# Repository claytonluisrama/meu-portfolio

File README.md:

# Meu Portfólio

Bem-vindo ao meu repositório de portfólio! Aqui você encontra uma coleção dos meus projetos acadêmicos e pessoais, demonstrando minhas habilidades e evolução profissional.

## Projetos Neste Repositório

### 1. Currículo Web (`/curriculo-web`)
[Clique aqui para acessar o site do meu Currículo Web!](https://claytonluisrama.github.io/meu-portfolio/curriculo-web/)

Um site estático desenvolvido em HTML que funciona como o meu currículo online. 
* **Tecnologias:** HTML
* **Objetivo:** Apresentar minha trajetória e habilidades de forma rápida e acessível.

### 2. Pedal de Guitarra (`/pedal-guitarra`)
Projeto de eletrônica de um pedal de guitarra.
* **Ferramentas:** KiCad
* **Objetivo:** Aplicar conhecimentos de esquemáticos e design de circuitos na prática.

---

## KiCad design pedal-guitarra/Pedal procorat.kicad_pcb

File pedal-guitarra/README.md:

# Projeto de Hardware: Pedal de Distorção (Baseado no ProCo RAT)

Este projeto é uma versão personalizada do icônico pedal de distorção **ProCo RAT**. O desenvolvimento envolveu desde o estudo do esquemático até a fabricação física da placa de circuito impresso (PCB).

## Especificações Técnicas
* **Controles:** 
  * `Gain`: Controle da intensidade da distorção.
  * `Filter`: Ajuste de corte de frequências (característica única do RAT).
  * `Volume`: Controle do nível de saída.
* **Componentes:** Resistores, capacitores (eletrolíticos e cerâmicos), diodos de clipagem e o amplificador operacional (Amp-Op).
* **Fabricação:** Placa produzida via corrosão em percloreto de ferro (ácido) e furação manual.

## Status do Projeto
Os arquivos do **KiCad* estão sendo refinados para documentar a versão final. O protótipo físico já está montado, testado e funcional.

## Processo de Fabricação e Resultado Final

### Placa de Circuito (Corrosão e Furação)
Aqui está o detalhe da PCB após o banho de ácido e a furação, pronta para receber os componentes:

### Pedal Finalizado
O resultado final do pedal montado na caixa:

---
*Este projeto faz parte do meu portfólio de Engenharia da Computação.*

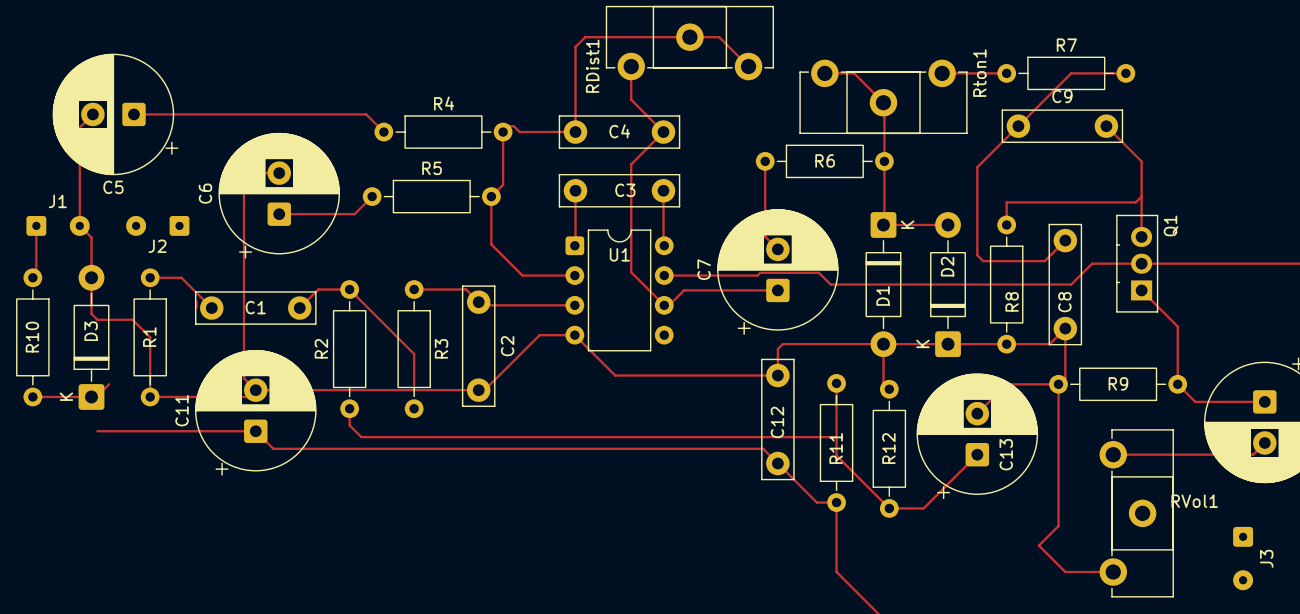
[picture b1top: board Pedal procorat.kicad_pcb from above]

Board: 2 copper layers, 36 parts (0 on the bottom side), 20 nets.

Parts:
C1, C9: 22n; C_Rect_L10.0mm_W2.5mm_P7.50mm_MKS4
C2: C; C_Rect_L10.0mm_W2.5mm_P7.50mm_MKS4
C3: 30p; C_Rect_L10.0mm_W2.5mm_P7.50mm_MKS4
C4: 100p; C_Rect_L10.0mm_W2.5mm_P7.50mm_MKS4
C5: 2,2u; CP_Radial_D10.0mm_P3.50mm
C6, C7: 4,7u; CP_Radial_D10.0mm_P3.50mm
C8: 3,3n; C_Rect_L10.0mm_W2.5mm_P7.50mm_MKS4
C10, C13: 1u; CP_Radial_D10.0mm_P3.50mm
C11: 100u; CP_Radial_D10.0mm_P3.50mm
C12: 0.1u; C_Rect_L10.0mm_W2.5mm_P7.50mm_MKS4
D1, D2: 1N914; D_DO-41_SOD81_P10.16mm_Horizontal
D3: 1N4002; D_DO-41_SOD81_P10.16mm_Horizontal
J1: +9V; SolderWire-0.127sqmm_1x02_P3.7mm_D0.48mm_OD1mm
J2: Audio in; SolderWire-0.127sqmm_1x02_P3.7mm_D0.48mm_OD1mm
J3: AudioJack2; SolderWire-0.127sqmm_1x02_P3.7mm_D0.48mm_OD1mm
Q1: BD436; TO-126-3_Vertical
R1, R2, R8: 1M; R_Axial_DIN0207_L6.3mm_D2.5mm_P10.16mm_Horizontal
R3, R6: 1k; R_Axial_DIN0207_L6.3mm_D2.5mm_P10.16mm_Horizontal
R4, R10: 47; R_Axial_DIN0207_L6.3mm_D2.5mm_P10.16mm_Horizontal
R5: 560; R_Axial_DIN0207_L6.3mm_D2.5mm_P10.16mm_Horizontal
R7: 1.5k; R_Axial_DIN0207_L6.3mm_D2.5mm_P10.16mm_Horizontal
R9: 10k; R_Axial_DIN0207_L6.3mm_D2.5mm_P10.16mm_Horizontal
R11, R12: 100K; R_Axial_DIN0207_L6.3mm_D2.5mm_P10.16mm_Horizontal
RDist1: 100k; Potentiometer_ACP_CA14-H2,5_Horizontal
RVol1: 100k; Potentiometer_ACP_CA14-H2,5_Horizontal
Rton1: 100k; Potentiometer_ACP_CA14-H2,5_Horizontal
U1: LM308; DIP-8_W7.62mm

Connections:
+9V: C11.1, C12.1, D3.1 (K), Q1.2 (C), R10.2, R11.1, U1.7 (V+)
Earth: C2.2, C5.2, C6.2, C8.2, C11.2, C12.2, C13.2, D1.2 (A), D2.1 (K), D3.2 (A), J1.2, R1.2, R8.2, R9.2, R12.2, RVol1.3, U1.4 (V-)
unnamed: C1.1, R2.2, R3.2
unnamed: C1.2, R1.1
unnamed: C5.1, R4.1
unnamed: C6.1, R5.1
unnamed: C7.2, R6.1
unnamed: C8.1, C9.1, R7.2
unnamed: C10.2, RVol1.1
unnamed: C13.1, R2.1, R11.2, R12.1
unnamed: D1.1 (K), D2.2 (A), R6.2, Rton1.2, Rton1.3
unnamed: J1.1, R10.1
unnamed: C9.2, Q1.3 (B), R8.1
unnamed: C10.1, Q1.1 (E), R9.1
unnamed: R7.1, Rton1.1
unnamed: C2.1, R3.1, U1.3 (+)
unnamed: C4.2, R4.2, R5.2, RDist1.2, RDist1.3, U1.2 (-)
unnamed: C3.1, U1.1 (C1)
unnamed: C3.2, U1.8 (C2)
unnamed: C4.1, C7.1, RDist1.1, U1.6 (OUT)

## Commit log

2026-05-11 Versao 1.0 - Adicionando site curriculo e projeto do pedal
2026-05-11 Adicionando README
2026-05-12 Colocando link do site no readme
2026-05-12 Adicionando fotos e detalhes tecnicos do pedal
2026-05-12 Readme Curriculo-Web
